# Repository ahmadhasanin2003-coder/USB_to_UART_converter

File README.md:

# USB Type-C to UART Converter

A custom USB Type-C to UART interface designed using the **CP2102 USB-to-UART bridge IC**.

## Overview

This project is a USB Type-C based UART converter that can be used to provide serial communication between a computer and embedded systems.

The design includes:

- USB Type-C receptacle for USB connectivity
- CP2102 USB-to-UART bridge
- USB ESD protection
- USB Type-C CC resistors
- UART TX/RX status LEDs
- External UART pins for easy connection to a microcontroller
- Power filtering and decoupling capacitors

## Block Diagram

```text
Computer
   │
   │ USB Type-C
   ▼
USB Type-C Connector
   │
   │ USB D+ / D-
   ▼
CP2102 USB-to-UART
   │
   ├── TX
   ├── RX
   └── VBUS
        │
        ▼
   External UART Pins

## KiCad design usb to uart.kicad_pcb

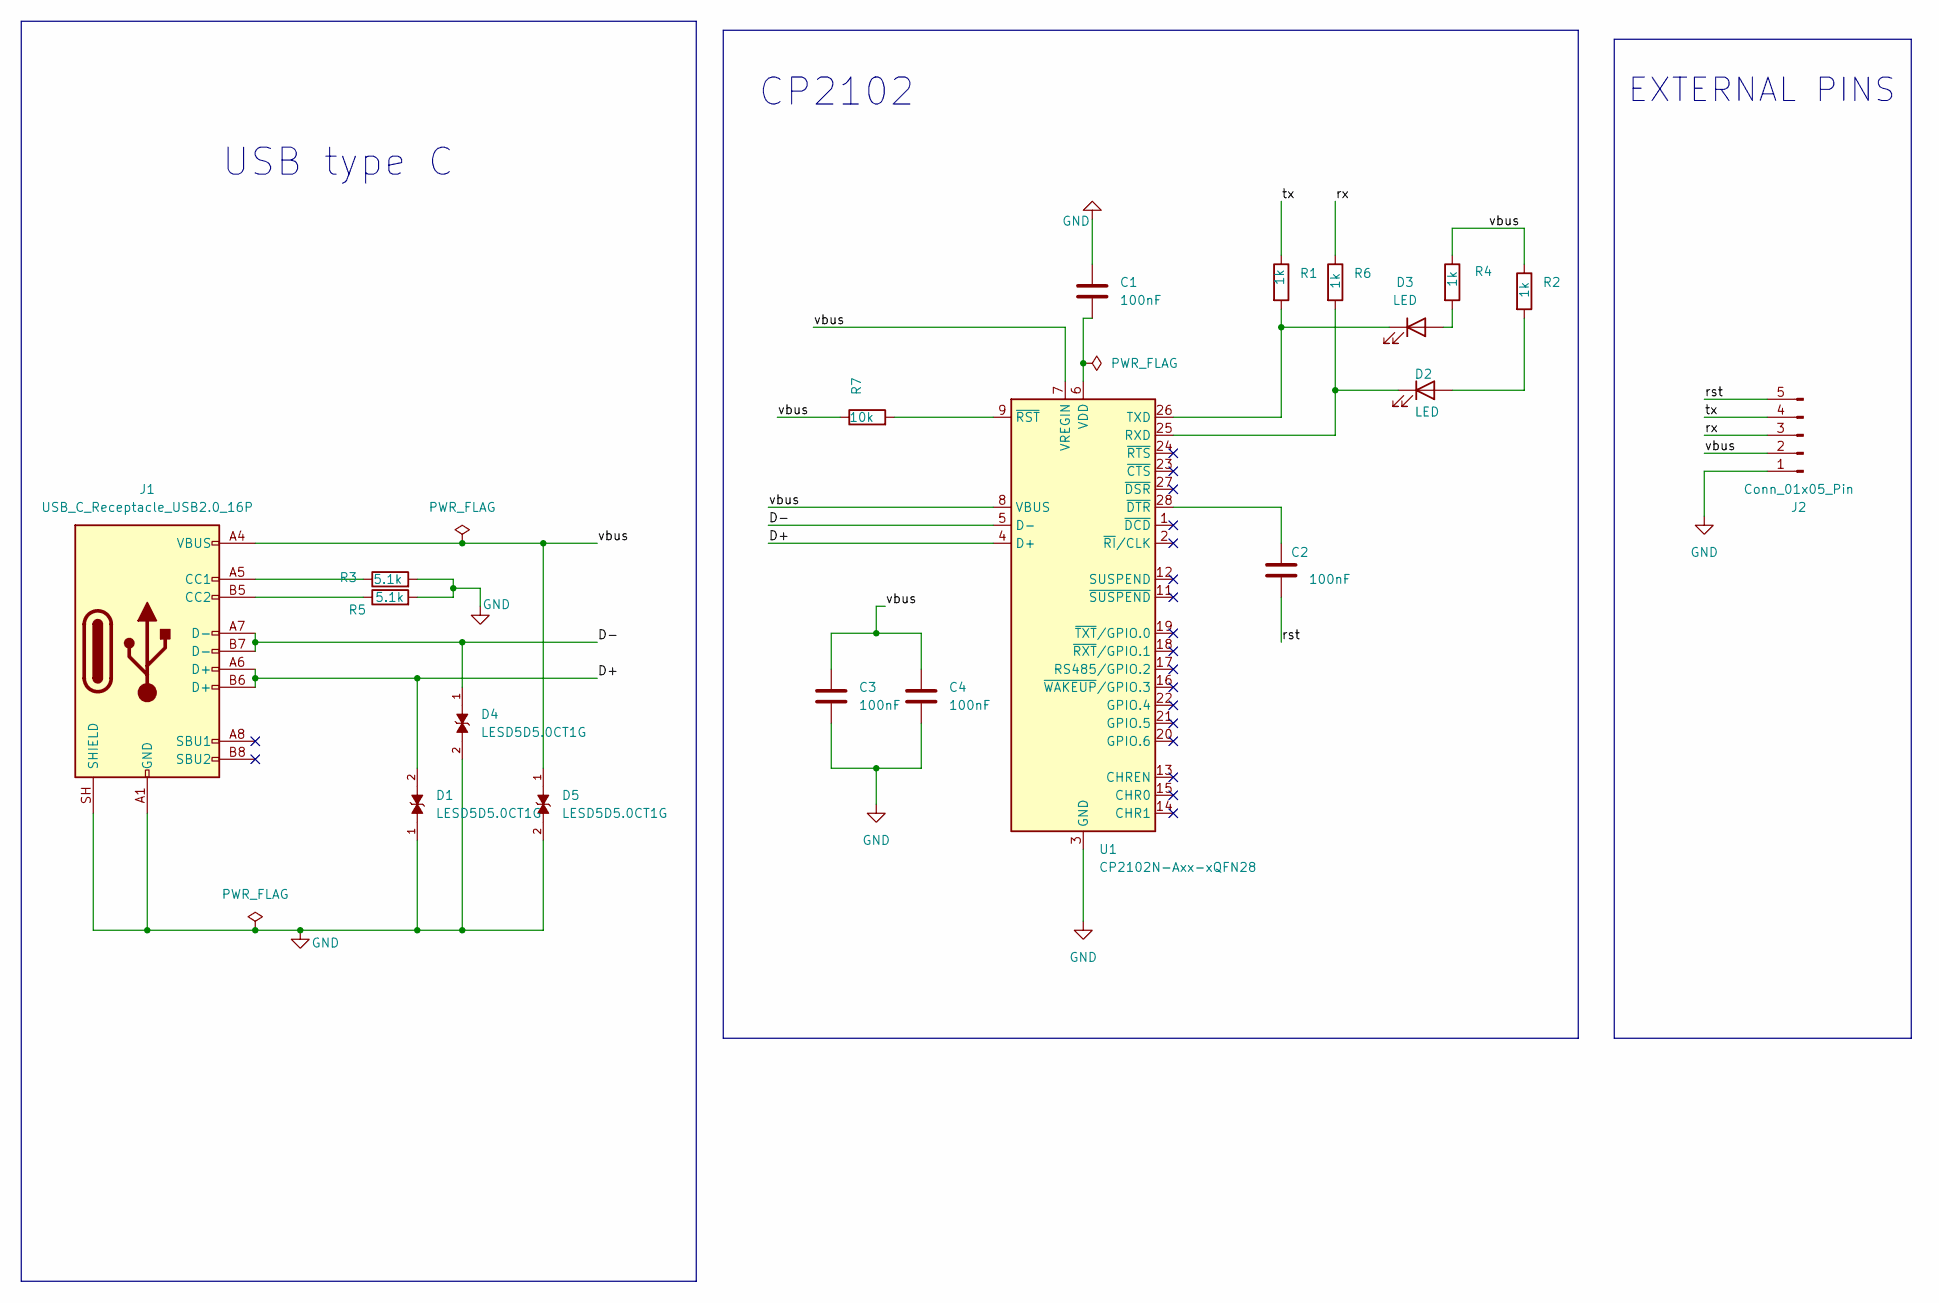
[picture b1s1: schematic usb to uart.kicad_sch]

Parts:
C1, C2, C3, C4: 100nF; C_0201_0603Metric
D1, D4, D5: LESD5D5.0CT1G; TVS_LESD5D5.0CT1G; PARTREV O
D2, D3: LED; LED_0201_0603Metric
J1: USB_C_Receptacle_USB2.0_16P; USB_C_Receptacle_HRO_TYPE-C-31-M-12
J2: Conn_01x05_Pin; PinHeader_1x05_P2.54mm_Horizontal
R1, R2, R4, R6: 1k; R_0201_0603Metric
R3, R5: 5.1k; R_0201_0603Metric
R7: 10k; R_0201_0603Metric
U1: CP2102N-Axx-xQFN28; QFN-28-1EP_5x5mm_P0.5mm_EP3.35x3.35mm

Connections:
/D+: D1.2, J1.A6 (D+), J1.B6 (D+), U1.4 (D+)
/D-: D4.1, J1.A7 (D-), J1.B7 (D-), U1.5 (D-)
/rst: C2.2, J2.5
/rx: J2.3, R6.1
/tx: J2.4, R1.1
/vbus: C3.1, C4.1, D5.1, J1.A4 (VBUS), J1.A9 (VBUS), J1.B4 (VBUS), J1.B9 (VBUS), J2.2, R2.1, R4.1, R7.1, U1.7 (VREGIN), U1.8 (VBUS)
GND: C1.1, C3.2, C4.2, D1.1, D4.2, D5.2, J1.A1 (GND), J1.A12 (GND), J1.B1 (GND), J1.B12 (GND), J1.SH (SHIELD), J2.1, R3.2, R5.2, U1.3 (GND), U1.29 (GND)
unnamed: D2.2 (A), R2.2
unnamed: D2.1 (K), R6.2, U1.25 (RXD)
unnamed: D3.2 (A), R4.2
unnamed: D3.1 (K), R1.2, U1.26 (TXD)
unnamed: J1.A5 (CC1), R3.1
unnamed: J1.B5 (CC2), R5.1
unnamed: C1.2, U1.6 (VDD)
unnamed: C2.1, U1.28 (~DTR)
unnamed: R7.2, U1.9 (~RST)

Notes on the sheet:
CP2102
USB type C
EXTERNAL PINS

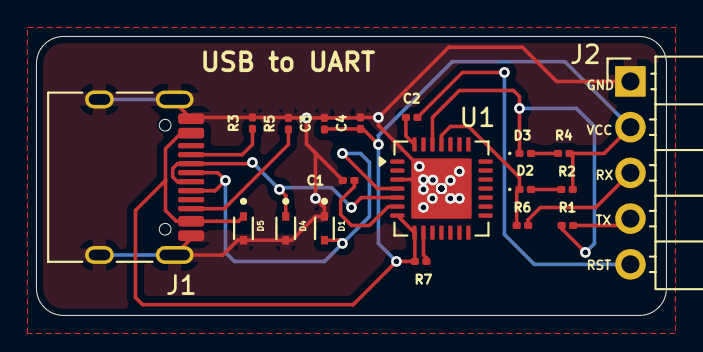
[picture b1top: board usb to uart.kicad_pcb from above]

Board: 2 copper layers, 35.0 x 15.5 mm, 19 parts (0 on the bottom side), 16 nets.
